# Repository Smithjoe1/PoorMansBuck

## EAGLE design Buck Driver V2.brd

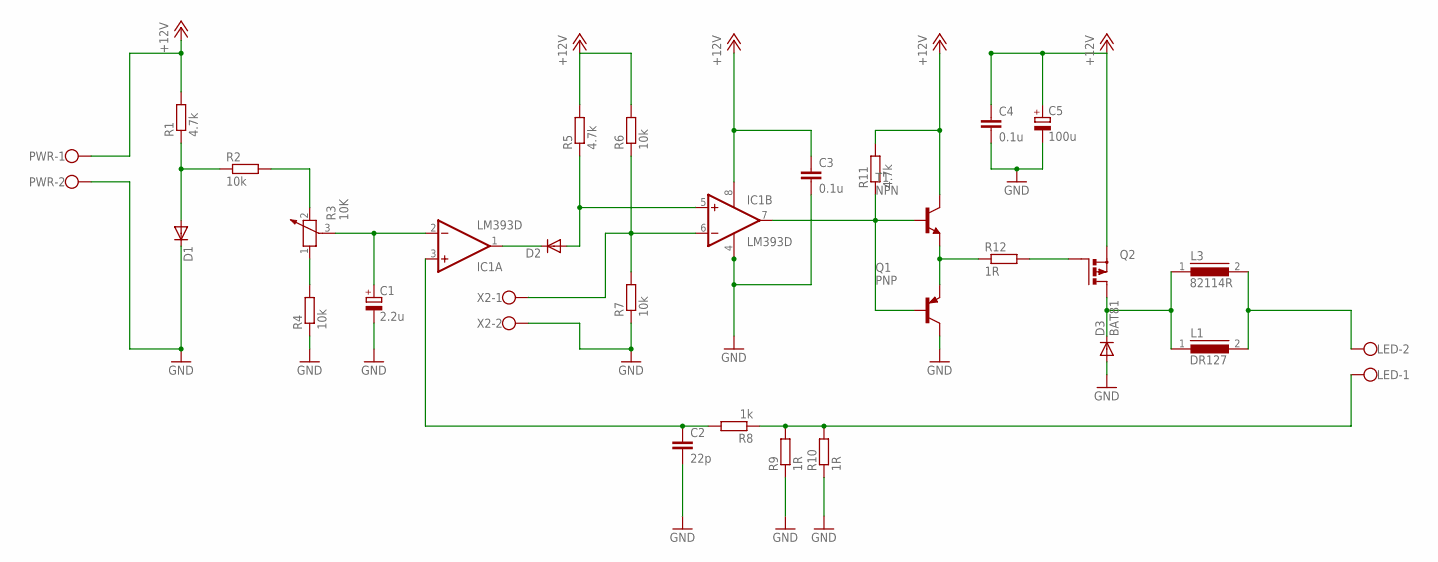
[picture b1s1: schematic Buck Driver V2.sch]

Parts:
C1: 2.2u; 140CLH-0810
C2: 22p; C1206
C3, C4: 0.1u; C1206
C5: 100u; 140CLH-0810
D1, D2: DIODE-DO214BA; DO214BA
D3: BAT81; DO34-7
IC1: LM393D; SO08
L1: DR127
L3: 82114R
LED: W237-102
PWR: W237-102
Q1: PNP; SOT23-BEC
Q2: PMOSFET_PTO220BH; TO220BH
R1, R5, R11: 4.7k; R1206
R2, R4, R6, R7: 10k; R1206
R3: 10K; PT-SPIN
R8: 1k; R1206
R9, R10: 1R; R2512
R12: 1R; R1206
T1: NPN; SOT23
X2: W237-102

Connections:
+12V: C3.1, C4.1, C5.+, IC1.8 (V+), PWR.1, Q2.S, R1.2, R5.2, R6.2, R11.2, T1.3 (C)
GND: C1.-, C2.2, C3.2, C4.2, C5.-, D1.C, D3.A, IC1.4 (V-), PWR.2, Q1.C, R4.1, R7.1, R9.1, R10.1, X2.2
unnamed: D1.A, R1.1, R2.1
unnamed: C1.+, IC1.2 (-IN), R3.3
unnamed: R3.1, R4.2
unnamed: R2.2, R3.2
unnamed: C2.1, IC1.3 (+IN), R8.2
unnamed: D2.C, IC1.1 (OUT)
unnamed: D2.A, IC1.5 (+IN), R5.1
unnamed: LED.1, R8.1, R9.2, R10.2
unnamed: Q1.E, R12.1, T1.2 (E)
unnamed: Q2.G, R12.2
unnamed: D3.C, L1.1, L3.1, Q2.D
unnamed: IC1.7 (OUT), Q1.B, R11.1, T1.1 (B)
unnamed: L1.2, L3.2, LED.2
PWM: IC1.6 (-IN), R6.1, R7.2, X2.1

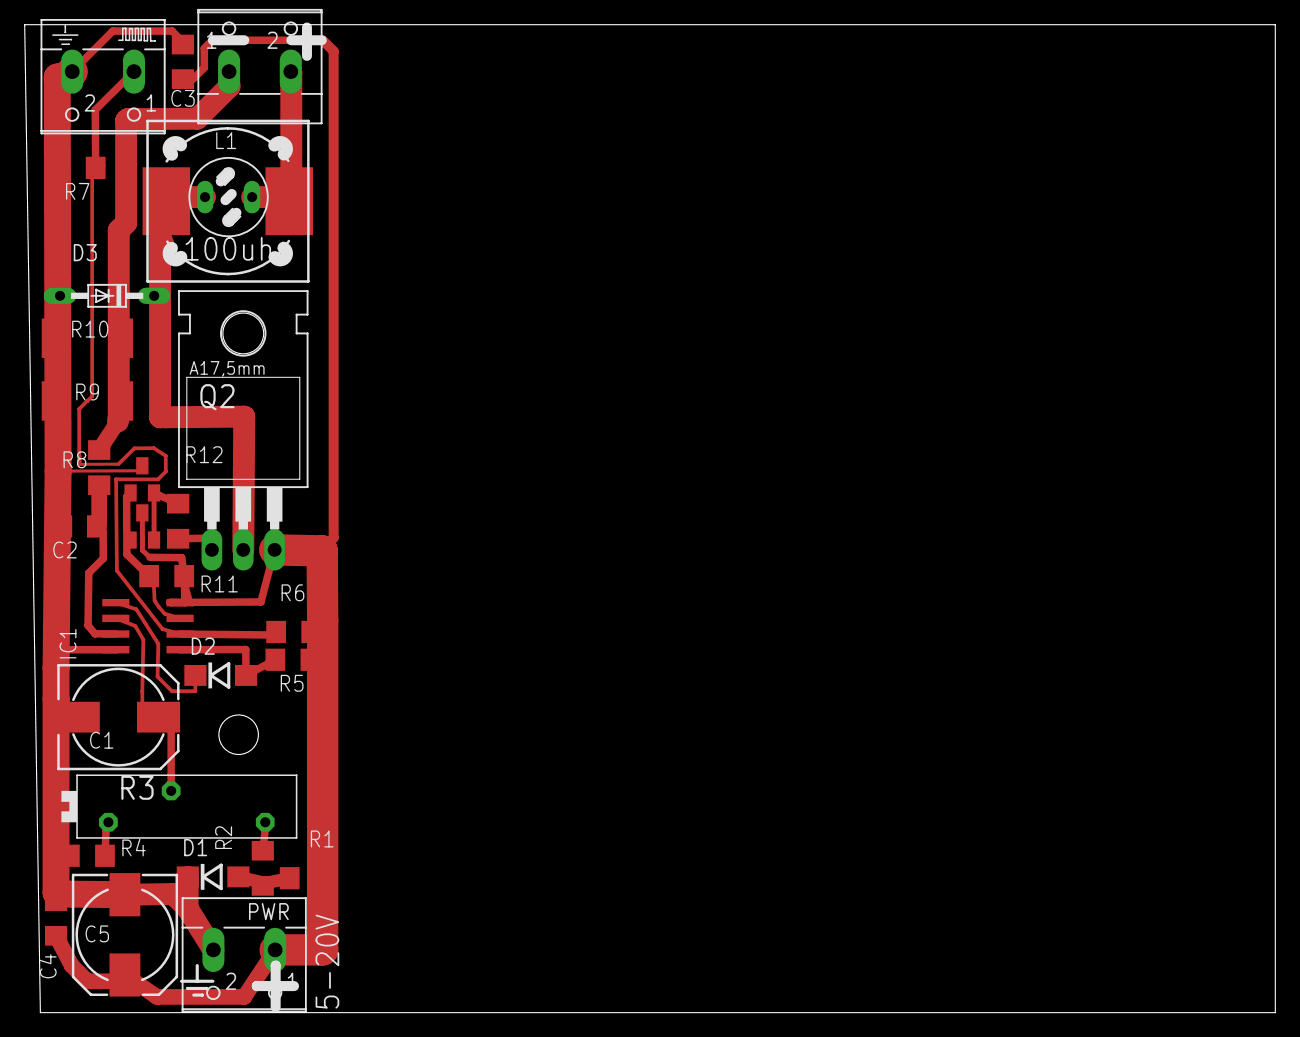
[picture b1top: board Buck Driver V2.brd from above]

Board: 2 copper layers, 101.3 x 80.0 mm, 29 parts (0 on the bottom side), 16 nets.
